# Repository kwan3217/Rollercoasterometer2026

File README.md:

Moved to [GitLab](https://gitlab.com/kwan32171/Rollercoasterometer2026)

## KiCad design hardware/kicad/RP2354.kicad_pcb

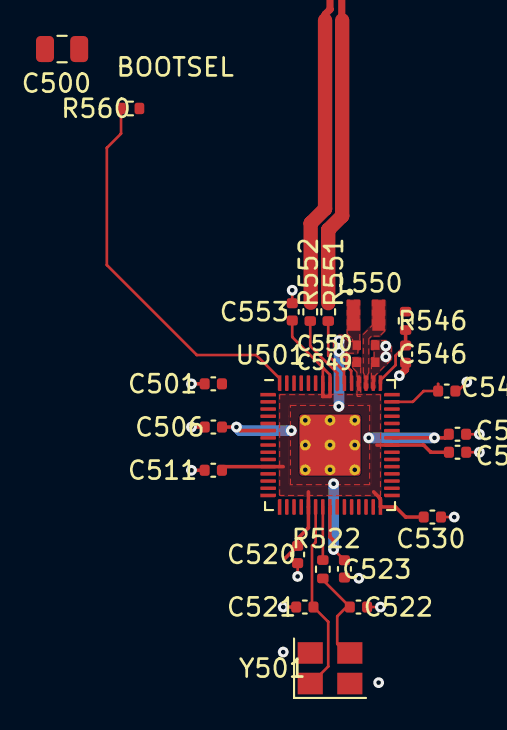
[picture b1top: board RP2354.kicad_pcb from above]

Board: 2 copper layers, 24 parts (0 on the bottom side), 11 nets.

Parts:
C500: 10u; C_0805_2012Metric
C501, C506, C511, C520, C530, C538, C539, C544, C553: 100n; C_0402_1005Metric
C521, C522: 15p; C_0402_1005Metric
C523, C546: 4.7u; C_0402_1005Metric
C549, C550: 4.7u; C_0402_1005Metric_small_pads
L550: 3.3u; L_pol_2016
R522, R560: 1k; R_0402_1005Metric
R546: 33; R_0402_1005Metric
R551, R552: 27; R_0402_1005Metric
U501: RP2350_60QFN; RP2350-QFN-60-1EP_7x7_P0.4mm_EP3.4x3.4mm_ThermalVias
Y501: ABM8-272-T3; Crystal_SMD_3225-4Pin_3.2x2.5mm

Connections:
+1V1: C506.1, C523.1, C539.1, C550.1, L550.1, U501.6 (DVDD), U501.23 (DVDD), U501.39 (DVDD), U501.50 (VREG_FB)
+3V3: C500.1, C501.1, C511.1, C520.1, C530.1, C538.1, C544.1, C549.1, C553.1, R546.1, U501.1 (IOVDD), U501.11 (IOVDD), U501.20 (IOVDD), U501.30 (IOVDD), U501.38 (IOVDD), U501.44 (ADC_AVDD), U501.45 (IOVDD), U501.49 (VREG_VIN), U501.53 (USB_OTP_VDD), U501.54 (QSPI_IOVDD)
/QSPI_SS: R560.1, U501.60 (QSPI_SS)
/VREG_AVDD: C546.1, R546.2, U501.46 (VREG_AVDD)
/VREG_LX: L550.2, U501.48 (VREG_LX)
/XIN: C521.1, U501.21 (XIN), Y501.1
/XOUT: R522.1, U501.22 (XOUT)
GND: C500.2, C501.2, C506.2, C511.2, C520.2, C521.2, C522.2, C523.2, C530.2, C538.2, C539.2, C544.2, C546.2, C549.2, C550.2, C553.2, U501.47 (VREG_PGND), U501.61 (GND), Y501.2, Y501.4
unnamed: C522.1, R522.2, Y501.3
unnamed: R551.2, U501.51 (USB_DM)
unnamed: R552.2, U501.52 (USB_DP)

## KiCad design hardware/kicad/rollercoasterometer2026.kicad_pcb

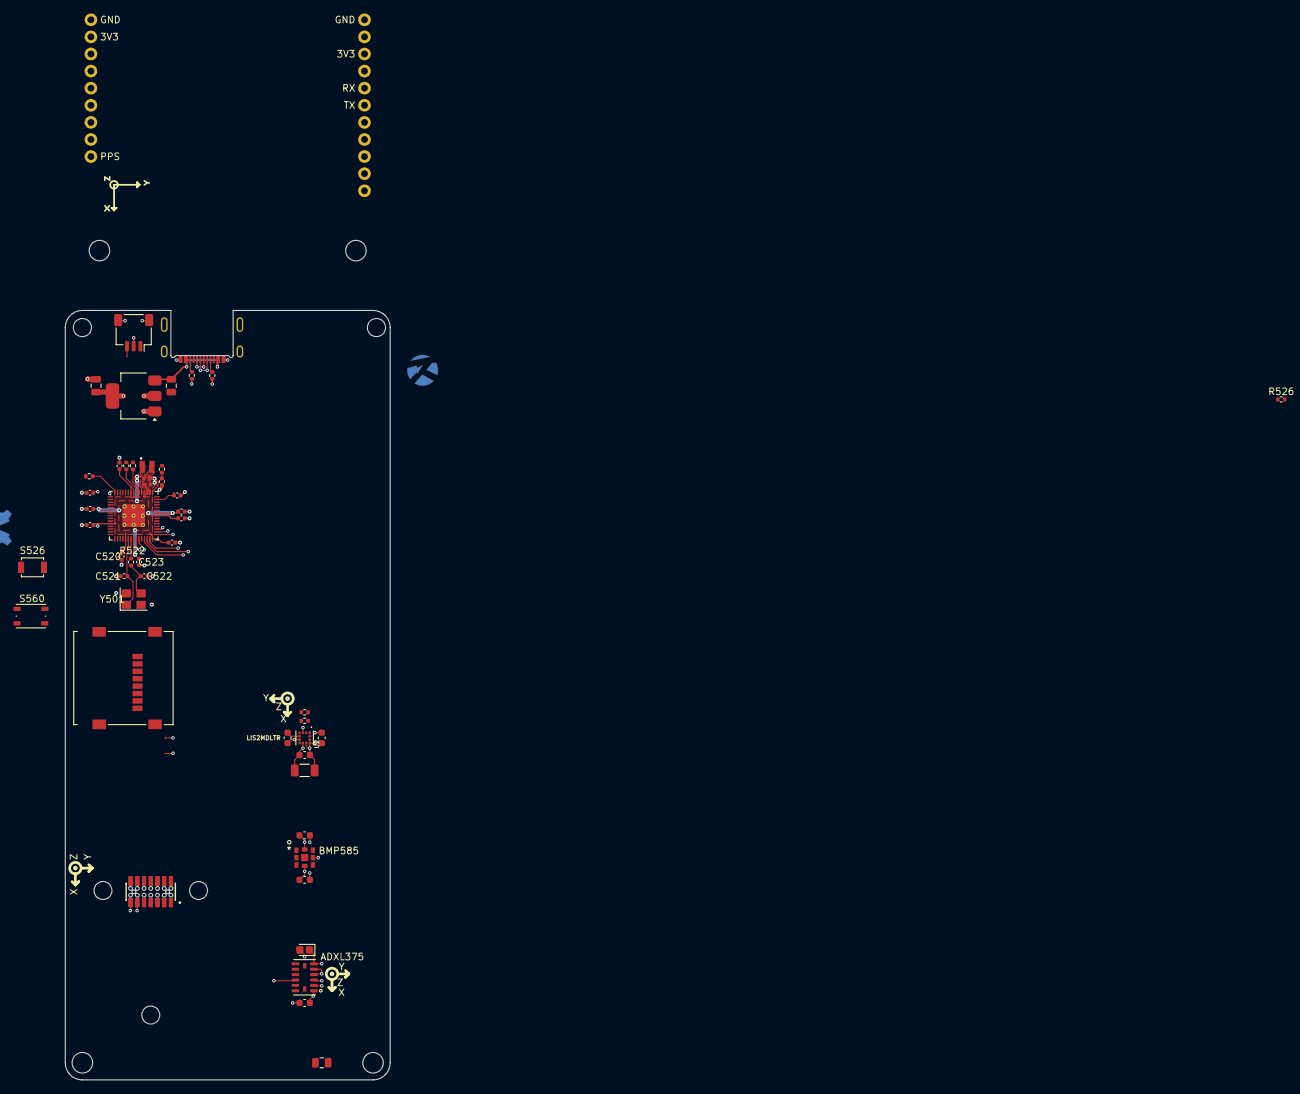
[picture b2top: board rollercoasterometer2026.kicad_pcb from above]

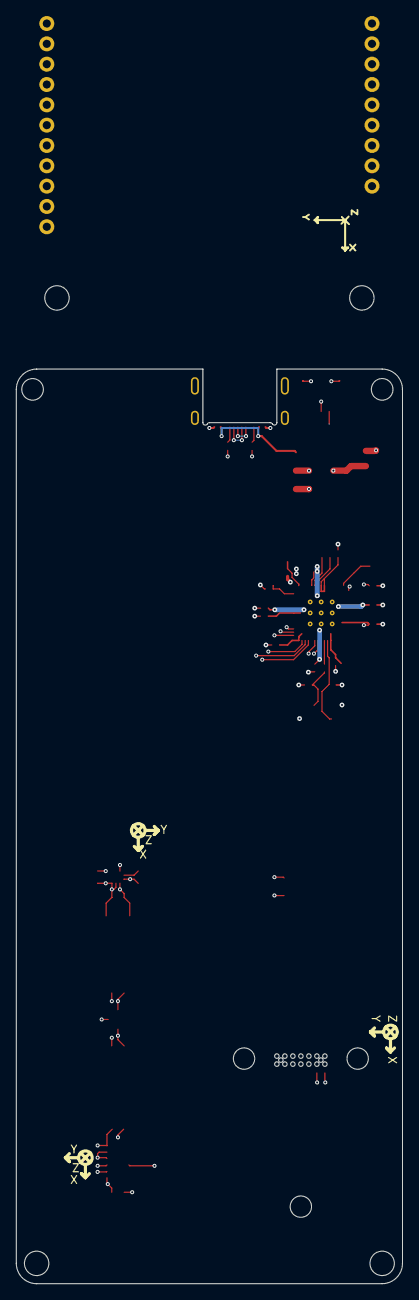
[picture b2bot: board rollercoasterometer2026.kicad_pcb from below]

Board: 4 copper layers, 48.3 x 114.3 mm, 60 parts (3 on the bottom side), 43 nets.

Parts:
C102, C103, C500: 10u; C_0805_2012Metric
C205: 220nF; C_0603_1608Metric
C208: 10uF; C_1206_3216Metric
C209, C210, C304, C308, C401: 100nF; C_0603_1608Metric
C406: 1uF tantalum; CP_EIA-1608-08_AVX-J
C501, C506, C511, C520, C530, C538, C539, C544, C553: 100n; C_0402_1005Metric
C521, C522: 15p; C_0402_1005Metric
C523, C546: 4.7u; C_0402_1005Metric
C549, C550: 4.7u; C_0402_1005Metric_small_pads
G101: Logo_Open_Hardware_Small; OSHW-Symbol_6.7x6mm_Copper
G102: Designed With; Symbol_KiCAD-Logo_CopperAndSilkScreenTop_small
G103: KwanSystems; StKwansSoldermask_0.6
G301: NOTE: Left Handed!; Axis_LH
G302: Axis
H101, H102, H103, H104: MountingHole; MountingHole_2.7mm_M2.5
J101: Micro_SD_Card; CONN_47219-2001_MOL
J102: Conn_02x07_Counter_Clockwise; SAMTEC_CLM-107-02-LM-D-A
J103: ZED-F9R U.FL; ZED-F9R_Breakout
J104: 2169900001; MOLEX_2169900001
J105: SM03B-SRSS-TB; JST_SH_SM03B-SRSS-TB_1x03-1MP_P1.00mm_Horizontal
L550: 3.3u; L_pol_2016
R101, R102: 5.1k; R_0402_1005Metric
R106, R107: 10k; R_0402_1005Metric
R522, R526, R560: 1k; R_0402_1005Metric
R546: 33; R_0402_1005Metric
R551, R552: 27; R_0402_1005Metric
S526: SW_Push; SW_SPST_B3U-1000P
S560: SW_Push; SW_Push_1P1T_NO_Vertical_Wuerth_434133025816
U2: LIS2MDLTR; PQFN50P200X200X70-12N
U101: NCP1117-3.3_SOT223; SOT-223-3_TabPin2
U102: ADIS16465-2BMLZ; ML-14-6_ADI
U301: BMP585; LGA9_BMP585_BOS
U401: ADXL375; LGA_CC-14-1_ADI
U501: RP2354A; RP2350-QFN-60-1EP_7x7_P0.4mm_EP3.4x3.4mm_ThermalVias
Y501: ABM8-272-T3; Crystal_SMD_3225-4Pin_3.2x2.5mm

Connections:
+3V3: C102.1, C208.1, C209.1, C210.1, C304.1, C308.1, C401.1, C406.1, C500.1, C501.1, C511.1, C520.1, C530.1, C538.1, C544.1, C549.1, C553.1, J101.4 (VDD), J102.11, J103.A8 (3V3), J103.B3 (3V3), R106.1, R107.1, R546.1, U2.3 (CS), U2.9 (VDD), U2.10 (VDD_IO), U101.2 (VO), U102.11 (VDD), U301.4 (VDDIO), U301.8 (VDD), U401.1 (VDDI/O), U401.3 (RESERVED), U401.6 (VS), U501.1 (IOVDD), U501.11 (IOVDD), U501.20 (IOVDD), U501.30 (IOVDD), U501.38 (IOVDD), U501.44 (ADC_AVDD), U501.45 (IOVDD), U501.49 (VREG_VIN), U501.53 (USB_OTP_VDD), U501.54 (QSPI_IOVDD)
/CC1: J104.A5 (CC1), R101.1
/CC2: J104.B5 (CC2), R102.2
/Controller/1V1: C506.1, C523.1, C539.1, C550.1, L550.1, U501.6 (DVDD), U501.23 (DVDD), U501.39 (DVDD), U501.50 (VREG_FB)
/Controller/QSPI_SS: R560.1, U501.60 (QSPI_SS)
/Controller/USB_D++: R552.2, U501.52 (USB_DP)
/Controller/USB_D--: R551.2, U501.51 (USB_DM)
/Controller/VREG_AVDD: C546.1, R546.2, U501.46 (VREG_AVDD)
/Controller/VREG_LX: L550.2, U501.48 (VREG_LX)
/Controller/XIN: C521.1, U501.21 (XIN), Y501.1
/Controller/XOUT: R522.1, U501.22 (XOUT)
/DR_BMP: U301.5 (INT), U501.32 (GPIO20)
/DR_HIG: U401.9 (INT2), U501.13 (GPIO9)
/DR_IMU: J102.1, U102.1 (DR), U501.5 (GPIO3)
/DR_MAG: U2.7 (INT/DRDY/SDO), U501.33 (GPIO21)
/MISO0: J102.4, U102.4 (DOUT), U301.3 (SDO), U401.12 (SDO), U501.27 (GPIO16)
/MISO1: J101.7 (DO), U501.16 (GPIO12)
/MOSI0: J102.5, U102.5 (DIN), U301.2 (SDX), U401.13 (SDI), U501.31 (GPIO19)
/MOSI1: J101.3 (DI), U501.15 (GPIO11)
/Magnetic Sensor/C1: C205.1, U2.5 (C1)
/PPS_GPS: J103.A1 (PPS), U501.4 (GPIO2)
/RX_GPS: J103.B5 (RX), U501.2 (GPIO0)
/SCK0: J102.3, U102.3 (SCLK), U301.1 (SCX), U401.14 (SCK), U501.29 (GPIO18)
/SCK1: J101.5 (CLK), U501.14 (GPIO10)
/SCL0: R107.2, U2.1 (SCL/SPC), U501.8 (GPIO5)
/SDA0: R106.2, U2.4 (SDA/SDI/SDO), U501.7 (GPIO4)
/SWCLK: J105.1, U501.24 (SWCLK)
/SWD: J105.3, U501.25 (SWD)
/SYNC_IMU: J102.2, U102.2 (SYNC), U501.19 (GPIO15)
/TX_GPS: J103.B6 (TX), U501.3 (GPIO1)
/USB_D+: J104.A6 (DA+), J104.B6 (DB+), R552.1
/USB_D-: J104.A7 (DA-), J104.B7 (DB-), R551.1
/~BOOT: R560.2, S560.2
/~CS_BMP: U301.7 (~CS), U501.9 (GPIO6)
/~CS_HIG: U401.7 (~CS), U501.12 (GPIO8)
/~CS_IMU: J102.6, U102.6 (~CS), U501.28 (GPIO17)
/~CS_SD: J101.2 (~CS), U501.17 (GPIO13)
/~RESET: S526.2, U501.26 (RUN)
/~RST_IMU: J102.8, U102.8 (~RST), U501.18 (GPIO14)
GND: C102.2, C103.2, C205.2, C208.2, C209.2, C210.2, C304.2, C308.2, C401.2, C406.2, C500.2, C501.2, C506.2, C511.2, C520.2, C521.2, C522.2, C523.2, C530.2, C538.2, C539.2, C544.2, C546.2, C549.2, C550.2, C553.2, J101.6 (VSS), J102.13, J103.A9 (GND), J103.B1 (GND), J104.A1_B12 (GND1), J104.B1_A12 (GND2), J105.2, J105.MP (MountPin), R101.2, R102.1, R526.2, S560.1, U2.6 (GND), U2.8 (GND__1), U101.1 (GND), U102.13 (GND), U301.6 (VSS), U401.2 (GND), U401.4 (GND), U401.5 (GND), U401.11 (RESERVED), U501.47 (VREG_PGND), U501.61 (GND), Y501.2, Y501.4
unnamed: C522.1, R522.2, Y501.3
unnamed: R526.1, S526.1
VBUS: C103.1, J104.A4_B9 (VBUS1), J104.B4_A9 (VBUS2), U101.3 (VI)

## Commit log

2026-02-17 Adding footprints
2026-02-17 Adding project library tables
2026-02-17 Adding subsheets
2026-02-17 Adding python source files
2026-02-17 Adding freecad model of bmp585
2026-02-17 Updated references to stp and wrl files
2026-02-17 Added cross section image
2026-02-17 Added molex microsd connector footprint
2026-02-17 Added iml files to gitignore
2026-02-17 Updated footprints for: * Courtyards with proper topology * Proper hole size * Circle instead of asterisk for pin 1 marker
2026-02-17 Updated board to four layer design
2026-02-18 Moved sensors from stamp to direct placement
2026-02-18 Started direct placement of RP2354
2026-02-18 Added symbol for Molex USB-C 21699-00001 receptacle
2026-02-21 Fixed edge.cuts outline for Molex USB-C 21699-00001 receptacle
2026-02-21 Import rp2354 module
2026-05-25 Update README to reflect project migration to GitLab
